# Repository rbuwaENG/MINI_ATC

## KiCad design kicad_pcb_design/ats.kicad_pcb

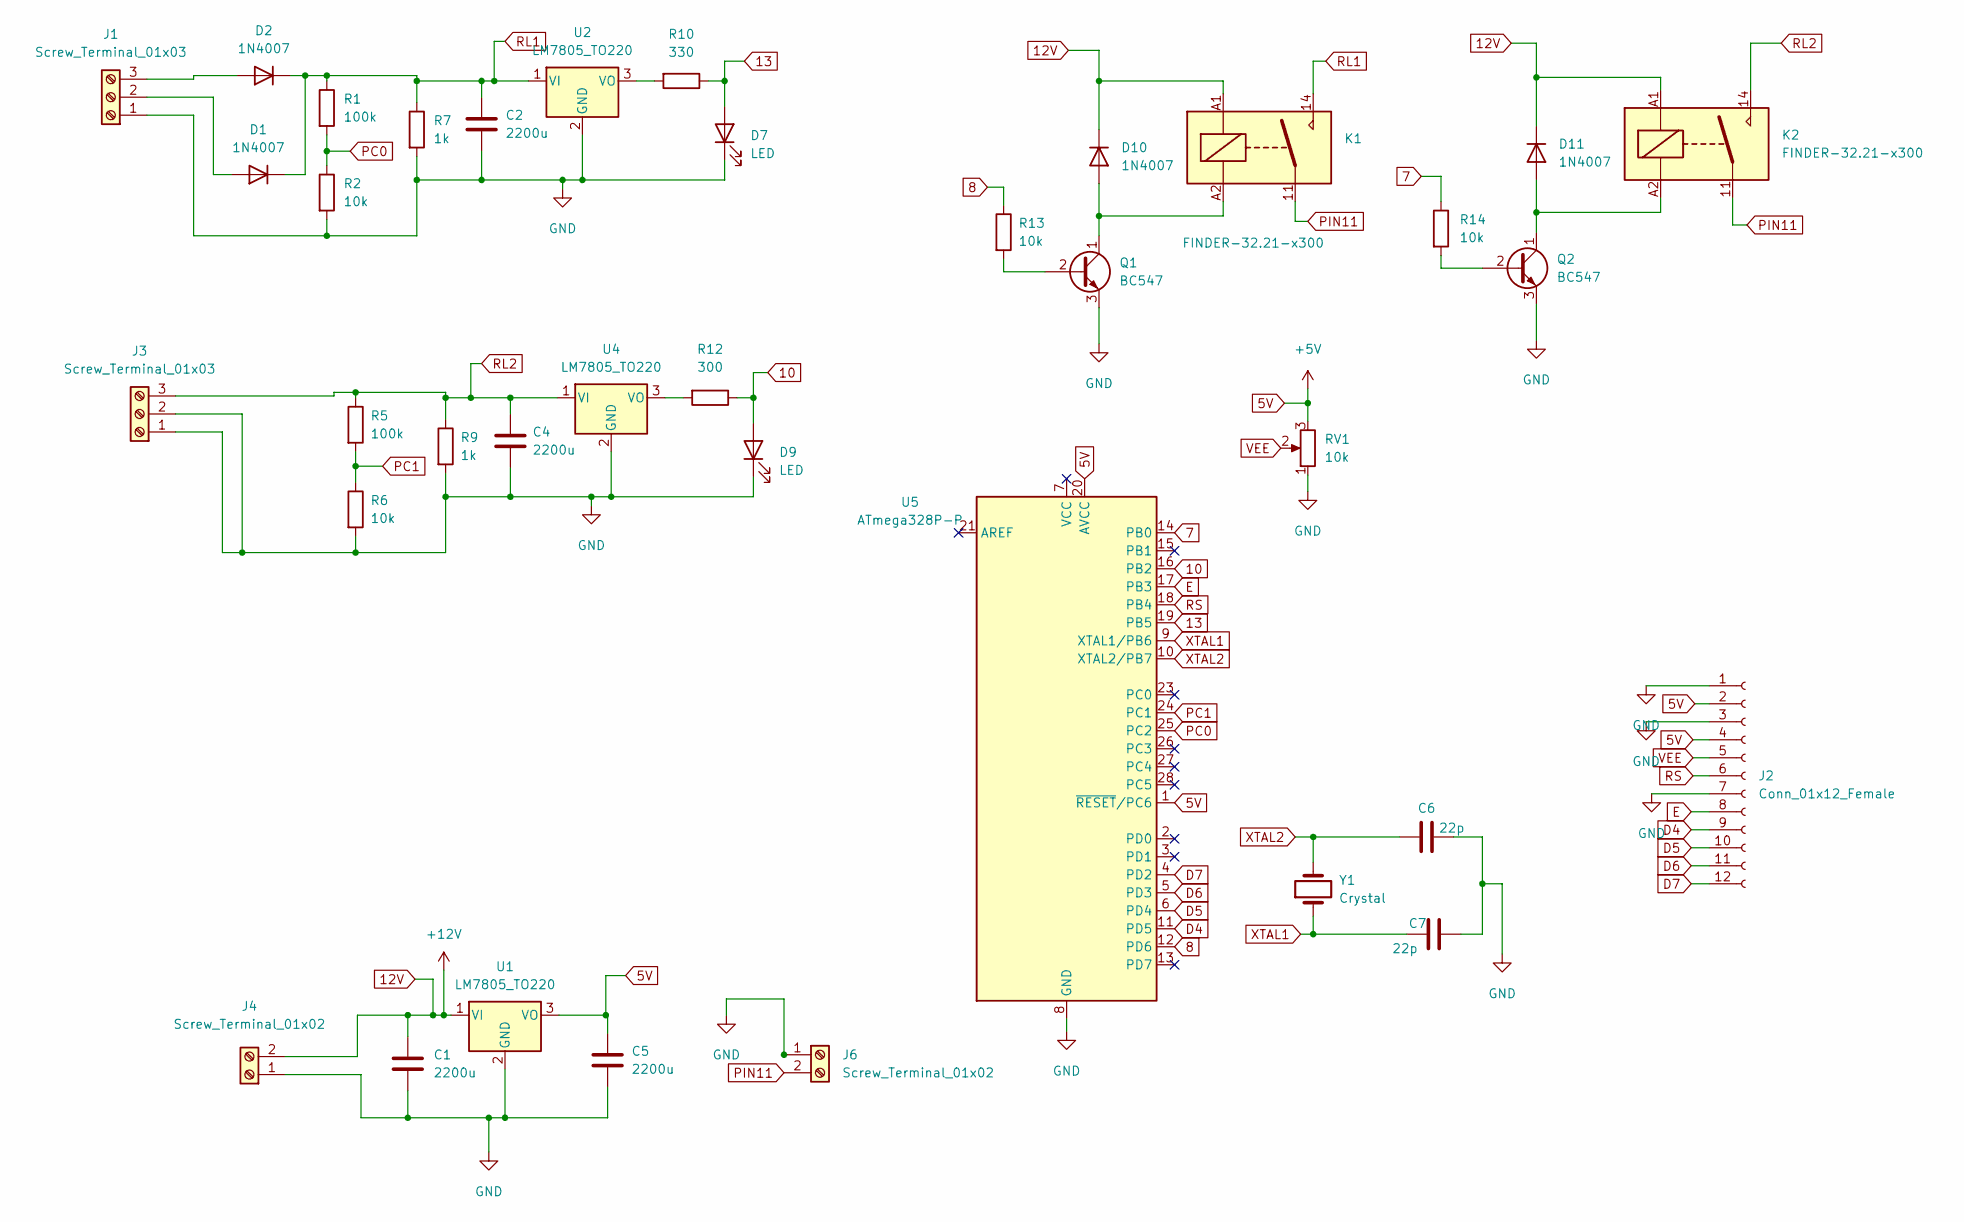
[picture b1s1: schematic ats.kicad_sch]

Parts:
C1, C2, C4, C5: 2200u; C_Radial_D10.0mm_H12.5mm_P5.00mm
C6, C7: 22p; C_Disc_D6.0mm_W2.5mm_P5.00mm
D1, D2, D10, D11: 1N4007; D_DO-41_SOD81_P10.16mm_Horizontal
D7, D9: LED; LED_D3.0mm
J1, J3: Screw_Terminal_01x03; TerminalBlock_Phoenix_MKDS-3-3-5.08_1x03_P5.08mm_Horizontal
J2: Conn_01x12_Female; PinHeader_1x12_P2.54mm_Vertical
J4: Screw_Terminal_01x02; TerminalBlock_Phoenix_MKDS-3-2-5.08_1x02_P5.08mm_Horizontal
J6: Screw_Terminal_01x02; TerminalBlock_Phoenix_MKDS-1,5-2-5.08_1x02_P5.08mm_Horizont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
K1, K2: FINDER-32.21-x300; Relay_SPDT_Finder_36.11
Q1, Q2: BC547; TO-92_Inline
R1, R5: 100k; R_Axial_DIN0204_L3.6mm_D1.6mm_P7.62mm_Horizontal
R2, R6, R13, R14: 10k; R_Axial_DIN0204_L3.6mm_D1.6mm_P7.62mm_Horizontal
R7, R9: 1k; R_Axial_DIN0204_L3.6mm_D1.6mm_P7.62mm_Horizontal
R10: 330; R_Axial_DIN0204_L3.6mm_D1.6mm_P7.62mm_Horizontal
R12: 300; R_Axial_DIN0204_L3.6mm_D1.6mm_P7.62mm_Horizontal
RV1: 10k; Potentiometer_Alps_RK163_Single_Horizontal
U1, U2, U4: LM7805_TO220; TO-220-3_Vertical
U5: ATmega328P-P; DIP-28_W7.62mm
Y1: Crystal; Crystal_HC18-U_Vertical

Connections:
5V: C5.1, J2.2, J2.4, RV1.3, U1.3 (VO), U5.1 (~RESET/PC6), U5.20 (AVCC)
7: R14.1, U5.14 (PB0)
8: R13.1, U5.12 (PD6)
10: D9.2 (A), R12.1, U5.16 (PB2)
12V: C1.1, D10.1 (K), D11.1 (K), J4.2, K1.A1, K2.A1, U1.1 (VI)
13: D7.2 (A), R10.1, U5.19 (PB5)
D4: J2.9, U5.11 (PD5)
D5: J2.10, U5.6 (PD4)
D6: J2.11, U5.5 (PD3)
D7: J2.12, U5.4 (PD2)
E: J2.8, U5.17 (PB3)
GND: C1.2, C2.2, C4.2, C5.2, C6.2, C7.2, D7.1 (K), D9.1 (K), J1.1, J2.1, J2.3, J2.7, J3.1, J3.2, J4.1, J6.1, Q1.3 (E), Q2.3 (E), R2.2, R6.2, R7.2, R9.2, RV1.1, U1.2 (GND), U2.2 (GND), U4.2 (GND), U5.8 (GND), U5.22 (GND)
unnamed: D1.2 (A), J1.2
unnamed: D2.2 (A), J1.3
unnamed: D10.2 (A), K1.A2, Q1.1 (C)
unnamed: D11.2 (A), K2.A2, Q2.1 (C)
unnamed: Q1.2 (B), R13.2
unnamed: Q2.2 (B), R14.2
unnamed: R10.2, U2.3 (VO)
unnamed: R12.2, U4.3 (VO)
PC0: R1.2, R2.1, U5.25 (PC2)
PC1: R5.2, R6.1, U5.24 (PC1)
PIN11: J6.2, K1.11, K2.11
RL1: C2.1, D1.1 (K), D2.1 (K), K1.14, R1.1, R7.1, U2.1 (VI)
RL2: C4.1, J3.3, K2.14, R5.1, R9.1, U4.1 (VI)
RS: J2.6, U5.18 (PB4)
VEE: J2.5, RV1.2
XTAL1: C7.1, U5.9 (XTAL1/PB6), Y1.1
XTAL2: C6.1, U5.10 (XTAL2/PB7), Y1.2

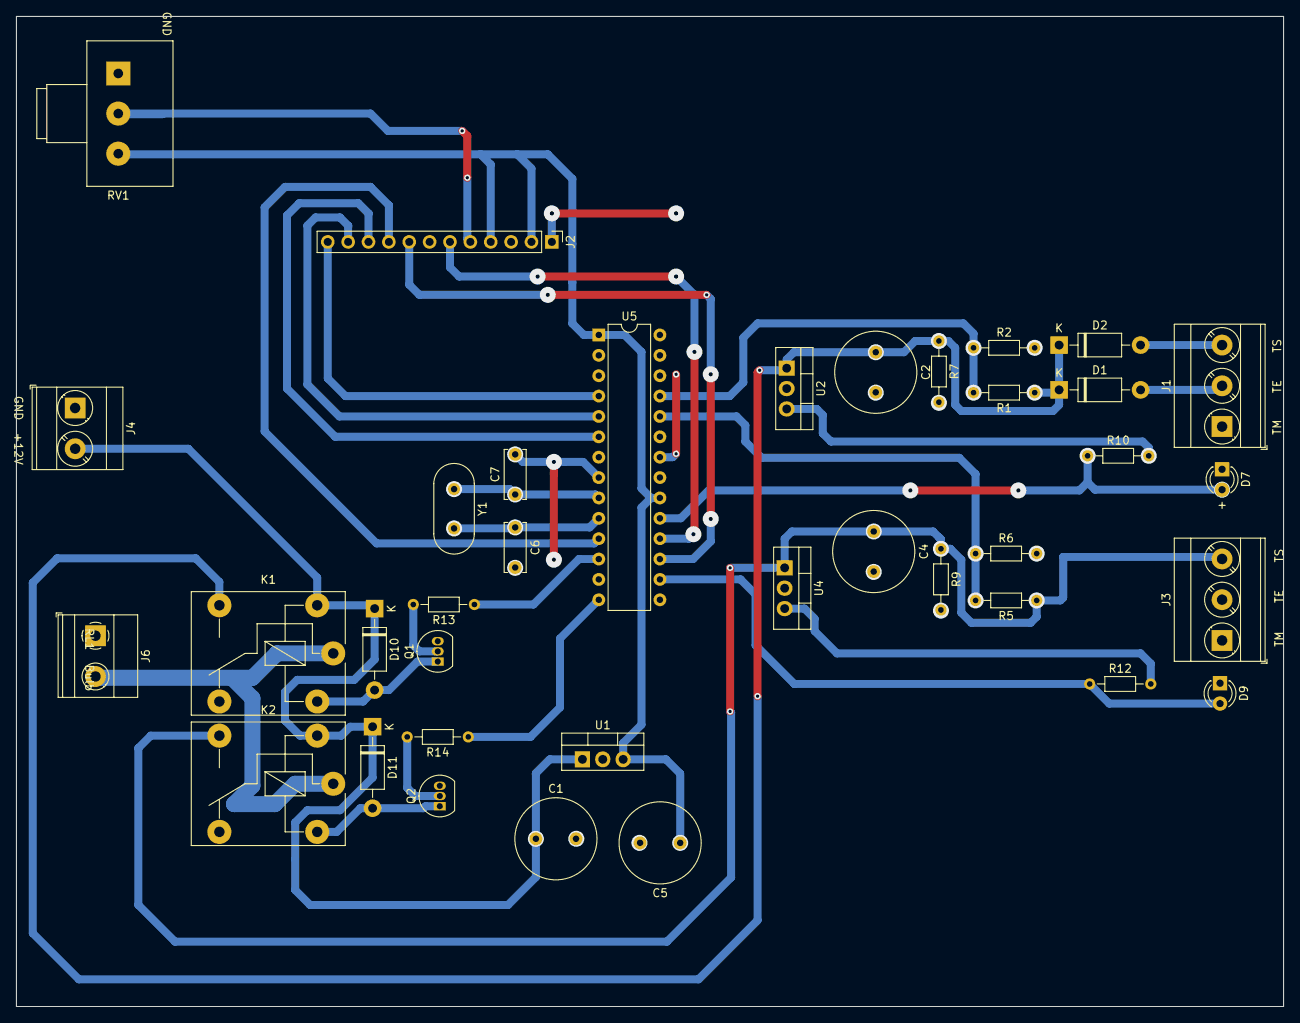
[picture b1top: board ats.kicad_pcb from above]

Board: 2 copper layers, 158.0 x 123.4 mm, 37 parts (0 on the bottom side), 29 nets.

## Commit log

2023-01-01 FINAL
